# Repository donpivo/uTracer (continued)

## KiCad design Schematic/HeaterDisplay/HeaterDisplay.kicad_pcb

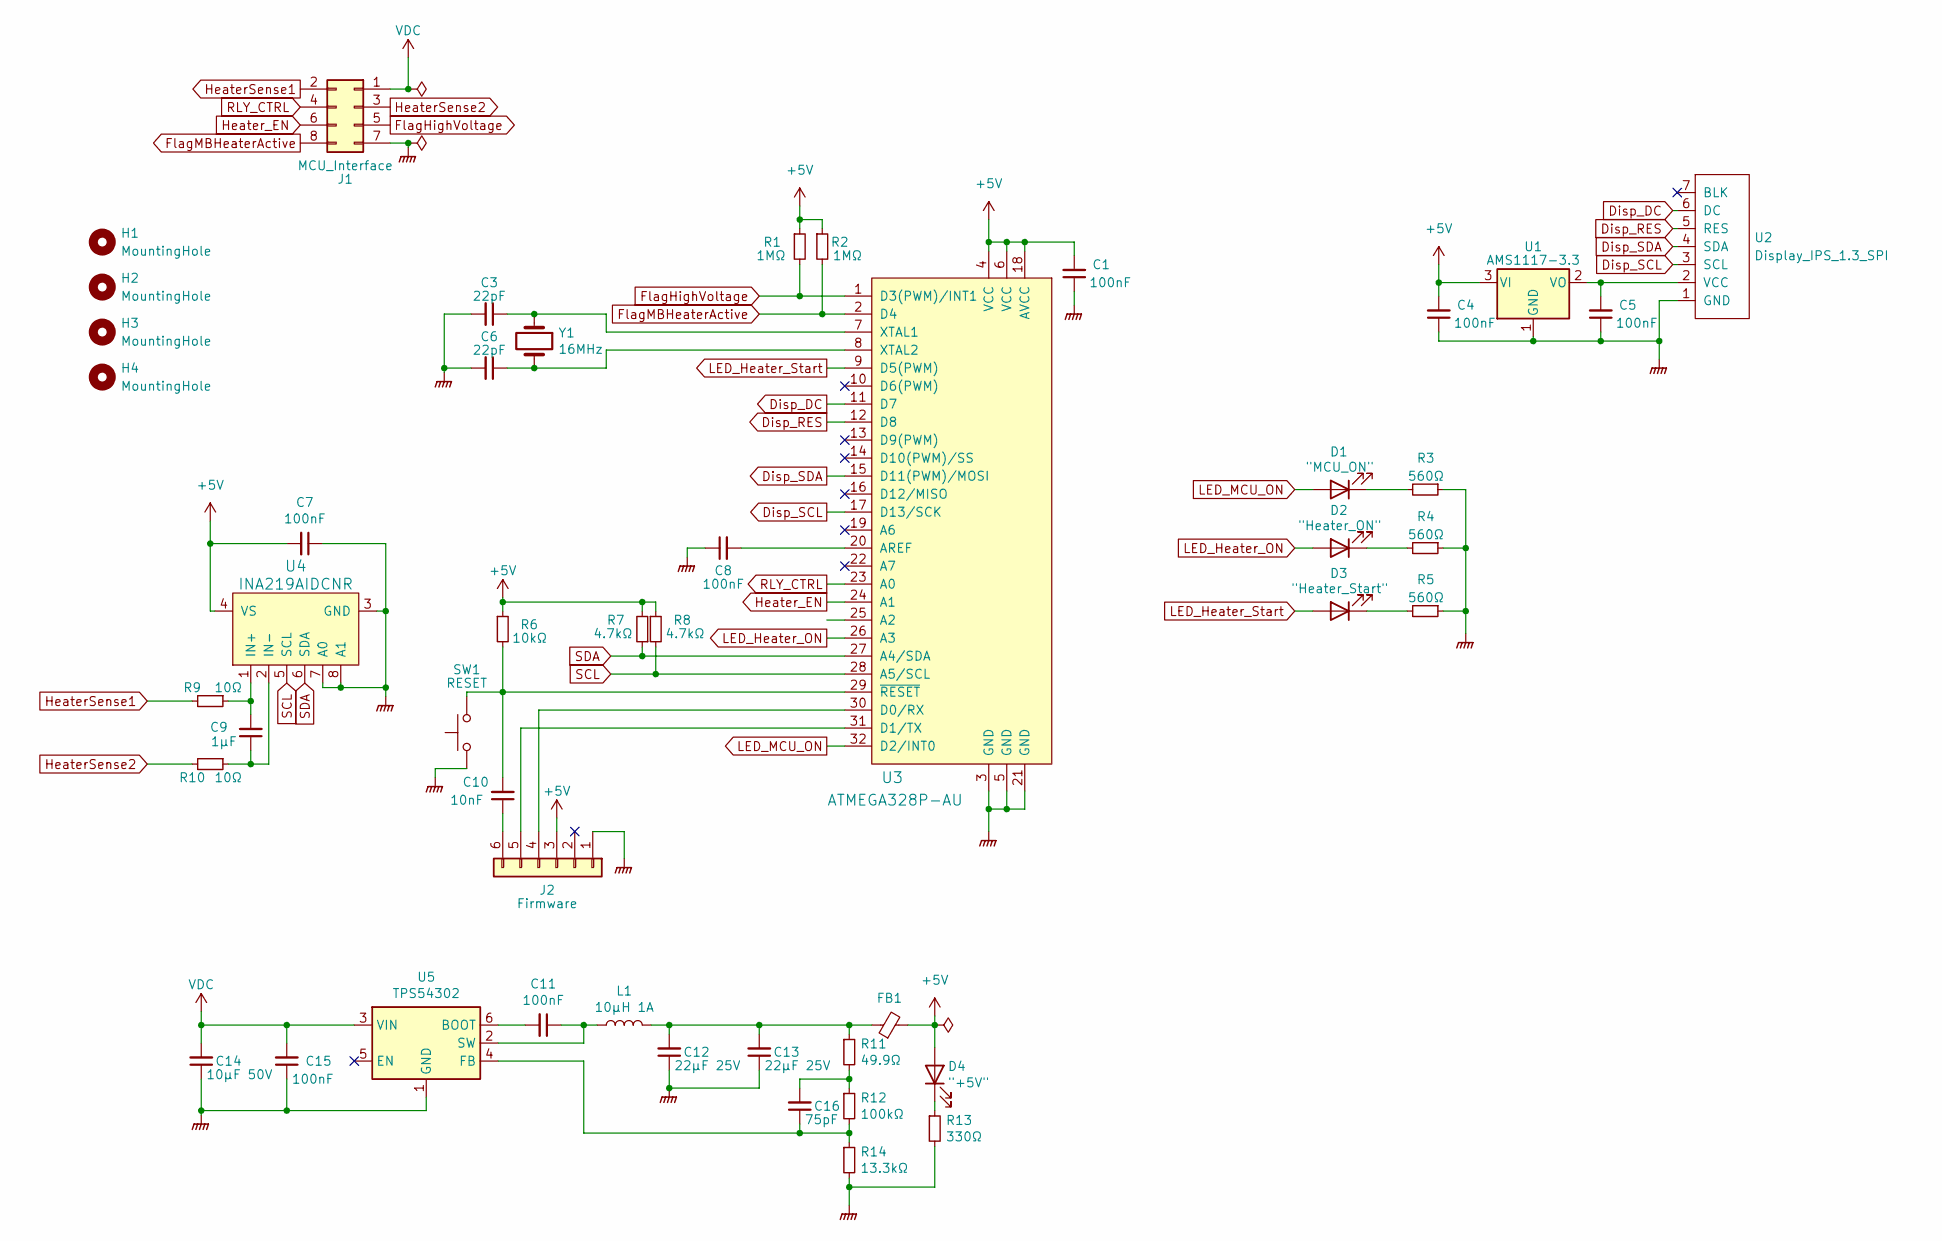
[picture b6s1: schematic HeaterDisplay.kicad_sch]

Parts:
C1, C4, C5, C7, C8, C11, C15: 100nF; C_0805_2012Metric_Pad1.18x1.45mm_HandSolder
C3, C6: 22pF; C_0805_2012Metric_Pad1.18x1.45mm_HandSolder
C9: 1µF; C_0805_2012Metric_Pad1.18x1.45mm_HandSolder
C10: 10nF; C_0805_2012Metric_Pad1.18x1.45mm_HandSolder
C12, C13: 22µF 25V; C_0805_2012Metric_Pad1.18x1.45mm_HandSolder
C14: 10µF 50V; C_0805_2012Metric_Pad1.18x1.45mm_HandSolder
C16: 75pF; C_0805_2012Metric_Pad1.18x1.45mm_HandSolder
D1: "MCU_ON"; LED_0805_2012Metric_Pad1.15x1.40mm_HandSolder
D2: "Heater_ON"; LED_0805_2012Metric_Pad1.15x1.40mm_HandSolder
D3: "Heater_Start"; LED_0805_2012Metric_Pad1.15x1.40mm_HandSolder
D4: "+5V"; LED_0805_2012Metric_Pad1.15x1.40mm_HandSolder
FB1: FerriteBead_Small; L_0805_2012Metric_Pad1.15x1.40mm_HandSolder
H1, H2, H3, H4: MountingHole; MountingHole_3.2mm_M3
J1: MCU_Interface; PinHeader_2x04_P2.54mm_Vertical
J2: Firmware; PinHeader_1x06_P2.54mm_Vertical
L1: 10µH 1A; L_Taiyo-Yuden_NR-20xx_HandSoldering
R1, R2: 1MΩ; R_0805_2012Metric_Pad1.20x1.40mm_HandSolder
R3, R4, R5: 560Ω; R_0805_2012Metric_Pad1.20x1.40mm_HandSolder
R6: 10kΩ; R_0805_2012Metric_Pad1.20x1.40mm_HandSolder
R7, R8: 4.7kΩ; R_0805_2012Metric_Pad1.20x1.40mm_HandSolder
R9, R10: 10Ω; R_0805_2012Metric_Pad1.20x1.40mm_HandSolder
R11: 49.9Ω; R_0805_2012Metric_Pad1.20x1.40mm_HandSolder
R12: 100kΩ; R_0805_2012Metric_Pad1.20x1.40mm_HandSolder
R13: 330Ω; R_0805_2012Metric_Pad1.20x1.40mm_HandSolder
R14: 13.3kΩ; R_0805_2012Metric_Pad1.20x1.40mm_HandSolder
SW1: RESET; SW_SPST_CK_RS282G05A3
U1: AMS1117-3.3; SOT-223-3_TabPin2
U2: Display_IPS_1.3_SPI
U3: ATMEGA328P-AU; TQFP-32_7x7mm
U4: INA219AIDCNR; SOT-23-8_Handsoldering; MPN INA219AIDCNR; Digi-Key_PN 296-23770-1-ND
U5: TPS54302; SOT-23-6_Handsoldering
Y1: 16MHz; Crystal_SMD_HC49-SD

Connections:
+5V: C1.2, C4.2, C7.2, D4.2 (A), FB1.2, J2.3, R1.1, R2.1, R6.1, R7.2, R8.1, U1.3 (VI), U3.4 (VCC), U3.6 (VCC), U3.18 (AVCC), U4.4 (VS)
Disp_DC: U2.6 (DC), U3.11 (D7)
Disp_RES: U2.5 (RES), U3.12 (D8)
Disp_SCL: U2.3 (SCL), U3.17 (D13/SCK)
Disp_SDA: U2.4 (SDA), U3.15 (D11(PWM)/MOSI)
FlagHighVoltage: J1.5, R1.2, U3.1 (D3(PWM)/INT1)
FlagMBHeaterActive: J1.8, R2.2, U3.2 (D4)
GNDPWR: C1.1, C3.2, C4.1, C5.1, C6.2, C7.1, C8.1, C12.1, C13.1, C14.1, C15.1, J1.7, J2.1, R3.1, R4.1, R5.1, R13.2, R14.2, SW1.1, U1.1 (GND), U2.1 (GND), U3.3 (GND), U3.5 (GND), U3.21 (GND), U4.3 (GND), U4.7 (A0), U4.8 (A1), U5.1 (GND)
HeaterSense1: J1.2, R9.2
HeaterSense2: J1.3, R10.2
Heater_EN: J1.6, U3.24 (A1)
LED_Heater_ON: D2.2 (A), U3.26 (A3)
LED_Heater_Start: D3.2 (A), U3.9 (D5(PWM))
LED_MCU_ON: D1.2 (A), U3.32 (D2/INT0)
unnamed: C3.1, U3.7 (XTAL1), Y1.1
unnamed: C5.2, U1.2 (VO), U2.2 (VCC)
unnamed: C6.1, U3.8 (XTAL2), Y1.2
unnamed: C10.1, J2.6
unnamed: C10.2, R6.2, SW1.2, U3.29 (~RESET)
unnamed: C11.1, L1.1, U5.2 (SW)
unnamed: C11.2, U5.6 (BOOT)
unnamed: C12.2, C13.2, FB1.1, L1.2, R11.1
unnamed: C16.1, R12.2, R14.1, U5.4 (FB)
unnamed: C16.2, R11.2, R12.1
unnamed: D1.1 (K), R3.2
unnamed: D2.1 (K), R4.2
unnamed: D3.1 (K), R5.2
unnamed: D4.1 (K), R13.1
unnamed: J2.4, U3.30 (D0/RX)
unnamed: J2.5, U3.31 (D1/TX)
unnamed: C9.2, R9.1, U4.1 (IN+)
unnamed: C9.1, R10.1, U4.2 (IN-)
unnamed: C8.2, U3.20 (AREF)
RLY_CTRL: J1.4, U3.23 (A0)
SCL: R8.2, U3.28 (A5/SCL), U4.5 (SCL)
SDA: R7.1, U3.27 (A4/SDA), U4.6 (SDA)
VDC: C14.2, C15.2, J1.1, U5.3 (VIN)

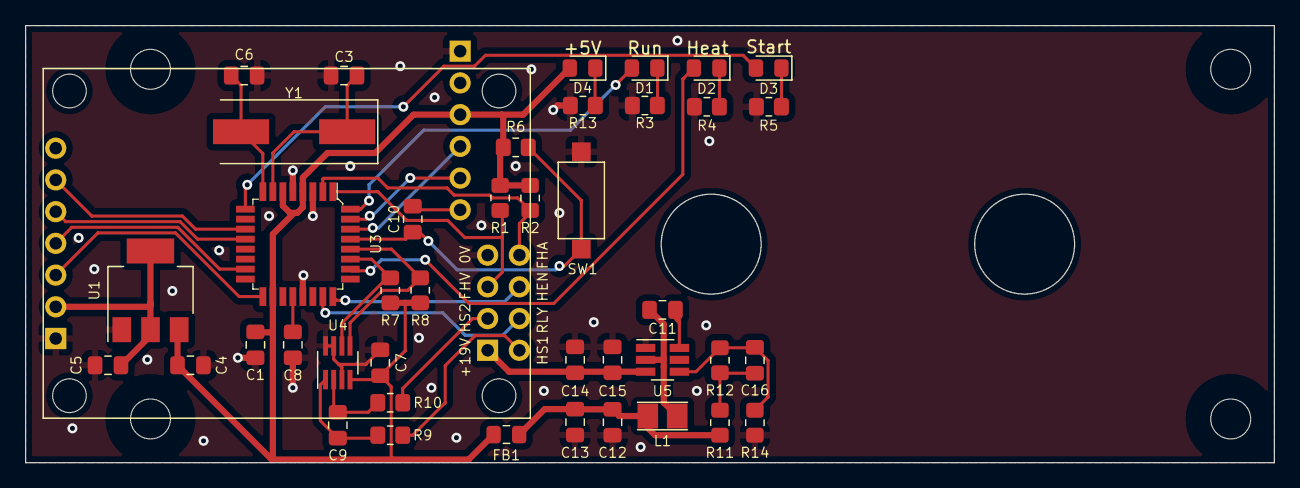
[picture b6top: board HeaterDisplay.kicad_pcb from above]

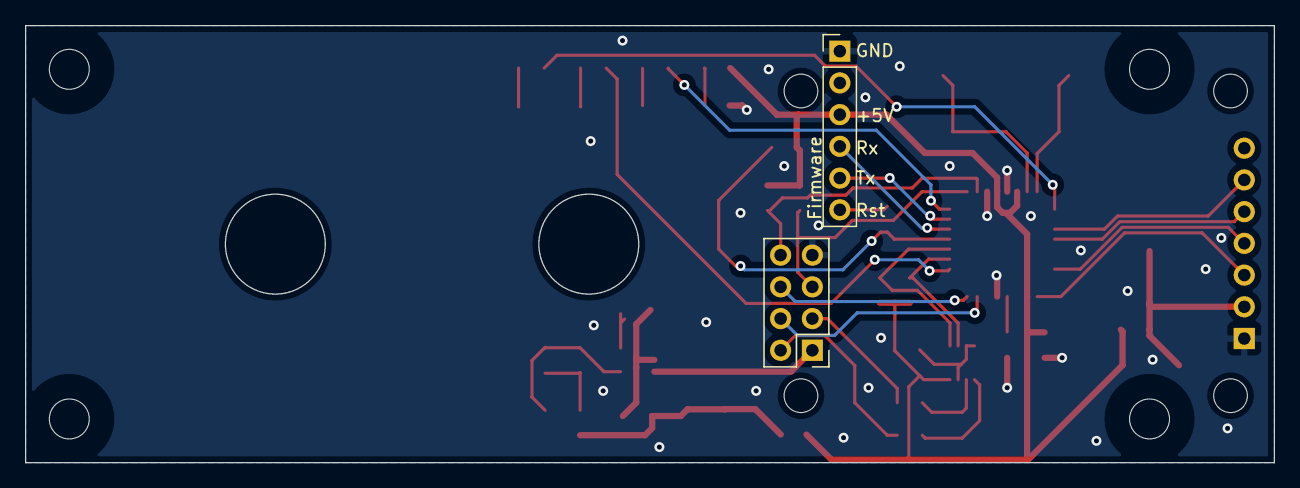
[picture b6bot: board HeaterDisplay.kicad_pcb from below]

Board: 2 copper layers, 100.0 x 35.0 mm, 48 parts (2 on the bottom side), 37 nets.

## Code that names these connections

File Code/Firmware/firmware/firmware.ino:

#include <Wire.h>
#include <INA219.h> //https://github.com/flav1972/ArduinoINA219
#include <SPI.h>
#include <Arduino_ST7789_Fast.h>
#include <Adafruit_GFX.h>

//INA219 Power Monitor Settings
#define SHUNT_MAX_V 0.03  
#define BUS_MAX_V   32.0  
#define MAX_CURRENT 5 
#define SHUNT_R   0.0105
INA219 ina219;

//Display Settings and Initialization
#define SCR_WD   240
#define SCR_HT   240
#define DISP_DC  10
#define DISP_RST 9
Arduino_ST7789 display = Arduino_ST7789(DISP_DC, DISP_RST);

//IO Pins
#define PIN_LED_MCU_STATUS 6
#define PIN_LED_HEATER A2
#define PIN_LED_HIGH_VOLTAGE A0
#define PIN_LED_LIMIT_I 3
#define PIN_LED_LIMIT_V 4
#define PIN_PSU_EN A1
#define PIN_OUT_EN A3
#define FLAG_HIGH_VOLTAGE 8
#define FLAG_HEATER_FILT 2
#define FLAG_CUR_LIM_FILT 5


//Global variables
bool heaterOn, prevHeaterOn;
bool currentLimited, prevCurrentLimited;
bool highVoltage, prevHighVoltage;
bool displayStatechange;
unsigned long lastMeasurementTime;
float lastVoltage=-1;
float lastCurrent=-1;

//Other settings
#define MEASUREMENT_INTERVAL 250 //milliseconds


void setup() 
{
  //Status LED: BOOT
  pinMode(PIN_LED_MCU_STATUS, OUTPUT);
  digitalWrite(PIN_LED_MCU_STATUS, LOW);
  //INA219 Power Monitor Initialization and Configuration
  ina219.begin();
  ina219.configure(INA219::RANGE_32V, INA219::GAIN_1_40MV, INA219::ADC_32SAMP, INA219::ADC_32SAMP, INA219::CONT_SH_BUS);
  ina219.calibrate(SHUNT_R, SHUNT_MAX_V, BUS_MAX_V, MAX_CURRENT);
  //Initialize and Clear Display
  display.init();
  display.setRotation(3);
  display.fillScreen(BLACK);
  //Configure IO pins
  pinMode(PIN_LED_HEATER, OUTPUT);
  pinMode(PIN_LED_HIGH_VOLTAGE, OUTPUT);
  pinMode(PIN_LED_LIMIT_I, OUTPUT);
  pinMode(PIN_LED_LIMIT_V, OUTPUT);
  pinMode(PIN_PSU_EN, OUTPUT);
  pinMode(PIN_OUT_EN, OUTPUT);
  pinMode(FLAG_HIGH_VOLTAGE, INPUT);
  pinMode(FLAG_HEATER_FILT, INPUT);
  pinMode(FLAG_CUR_LIM_FILT, INPUT);
  digitalWrite(PIN_PSU_EN, HIGH);
  digitalWrite(PIN_LED_LIMIT_V, HIGH);
  digitalWrite(PIN_LED_MCU_STATUS, HIGH);
}

void loop() 
{
  heaterOn=!digitalRead(FLAG_HEATER_FILT);
  // heaterOn=true;
  if(heaterOn!=prevHeaterOn)
  {
    digitalWrite(PIN_LED_HEATER, heaterOn);
    digitalWrite(PIN_OUT_EN, heaterOn);
    displayStatechange=true;
    prevHeaterOn=heaterOn;
  }
  
  currentLimited=!digitalRead(FLAG_CUR_LIM_FILT);
  // currentLimited=true;
  if(currentLimited!=prevCurrentLimited)
  {
    digitalWrite(PIN_LED_LIMIT_I, currentLimited);
    digitalWrite(PIN_LED_LIMIT_V, !currentLimited);
    displayStatechange=true;
    prevCurrentLimited=currentLimited;
  }
  
  highVoltage=digitalRead(FLAG_HIGH_VOLTAGE);
  // highVoltage=true;
  if(highVoltage!=prevHighVoltage)
  {
    digitalWrite(PIN_LED_HIGH_VOLTAGE, highVoltage);
    displayStatechange=true;
    prevHighVoltage=highVoltage;
  }  
  
  if(millis()-lastMeasurementTime>MEASUREMENT_INTERVAL)
  {
    
    float voltage=round1(ina219.busVoltage());
    if(voltage!=lastVoltage)
    {
      updateDisplayVoltage(voltage);
      lastVoltage=voltage;
    }
    float current=round1(ina219.shuntCurrent());
    if(current!=lastCurrent)
    {
      updateDisplayCurrent(current);
      lastCurrent=current;
    }
    if(displayStatechange) updateDisplayStatus();
    lastMeasurementTime=millis();

  }
}



float round1(float value) {
   return (int)(value * 10) / 10.0;
}

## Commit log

2022-10-30 First draft
2022-10-30 Minor layout changes
2022-10-30 Added Power Input board
2022-10-31 Added filtering on PSU1 secondary
2022-11-03 Added holders for EMI shield
2022-11-14 Larger mounting hole for rotary switch
2022-11-14 Added load resistor, updated annotation, changed NTC footprint
2022-11-14 Changed inductor footprint
2022-11-14 Updated annotation
2022-11-18 Added filtering caps for heater elevation
2022-12-02 Changed resistor values
2022-12-03 MCU Board adapted for 3.3V operation
2022-12-04 Optocouplers moved to from PSU to MCU board
2022-12-04 Swapped IO pins
2022-12-04 Added PWM controlled MOSFET output for soft start
2022-12-05 Added 12V regulator for PWM output driver
2022-12-20 Updated component values
2022-12-20 Added test code for display and power monitor
2022-12-26 New PSU based on XL4005
    Added current limiter
    Added interface to uTracer PIC
2022-12-28 Changed DC in label: 9V
2023-01-05 PIC interface board, version A
2023-01-11 Rearranged schematic
2023-01-11 Updated pin names
2023-01-11 Changed pin for MCU status LED
2023-01-12 Adjusted position for potmeter hole
2023-01-22 Added output filter caps + spacing around mounting holes
2023-01-23 New status LED layout
2023-01-23 Changed LED footprints to 0603
2023-01-23 Added indent in PCB for FFC cable
2023-02-12 Added project pictures
2023-02-12 Firmware, first draft
2023-02-12 Changed component values
2023-02-17 Adjusted display text positions
2023-02-17 4 screw attachment for front panel
2023-02-20 Fixed display update bug
2023-02-24 Added Front panel labels
2023-02-24 Removed irrelevant datasheet
2023-03-11 Digital heater PSU, first draft
2023-03-12 Added driver stage for output MOSFET
2023-05-01 File cleanup
2023-05-12 Added BOM (bill of materials)
